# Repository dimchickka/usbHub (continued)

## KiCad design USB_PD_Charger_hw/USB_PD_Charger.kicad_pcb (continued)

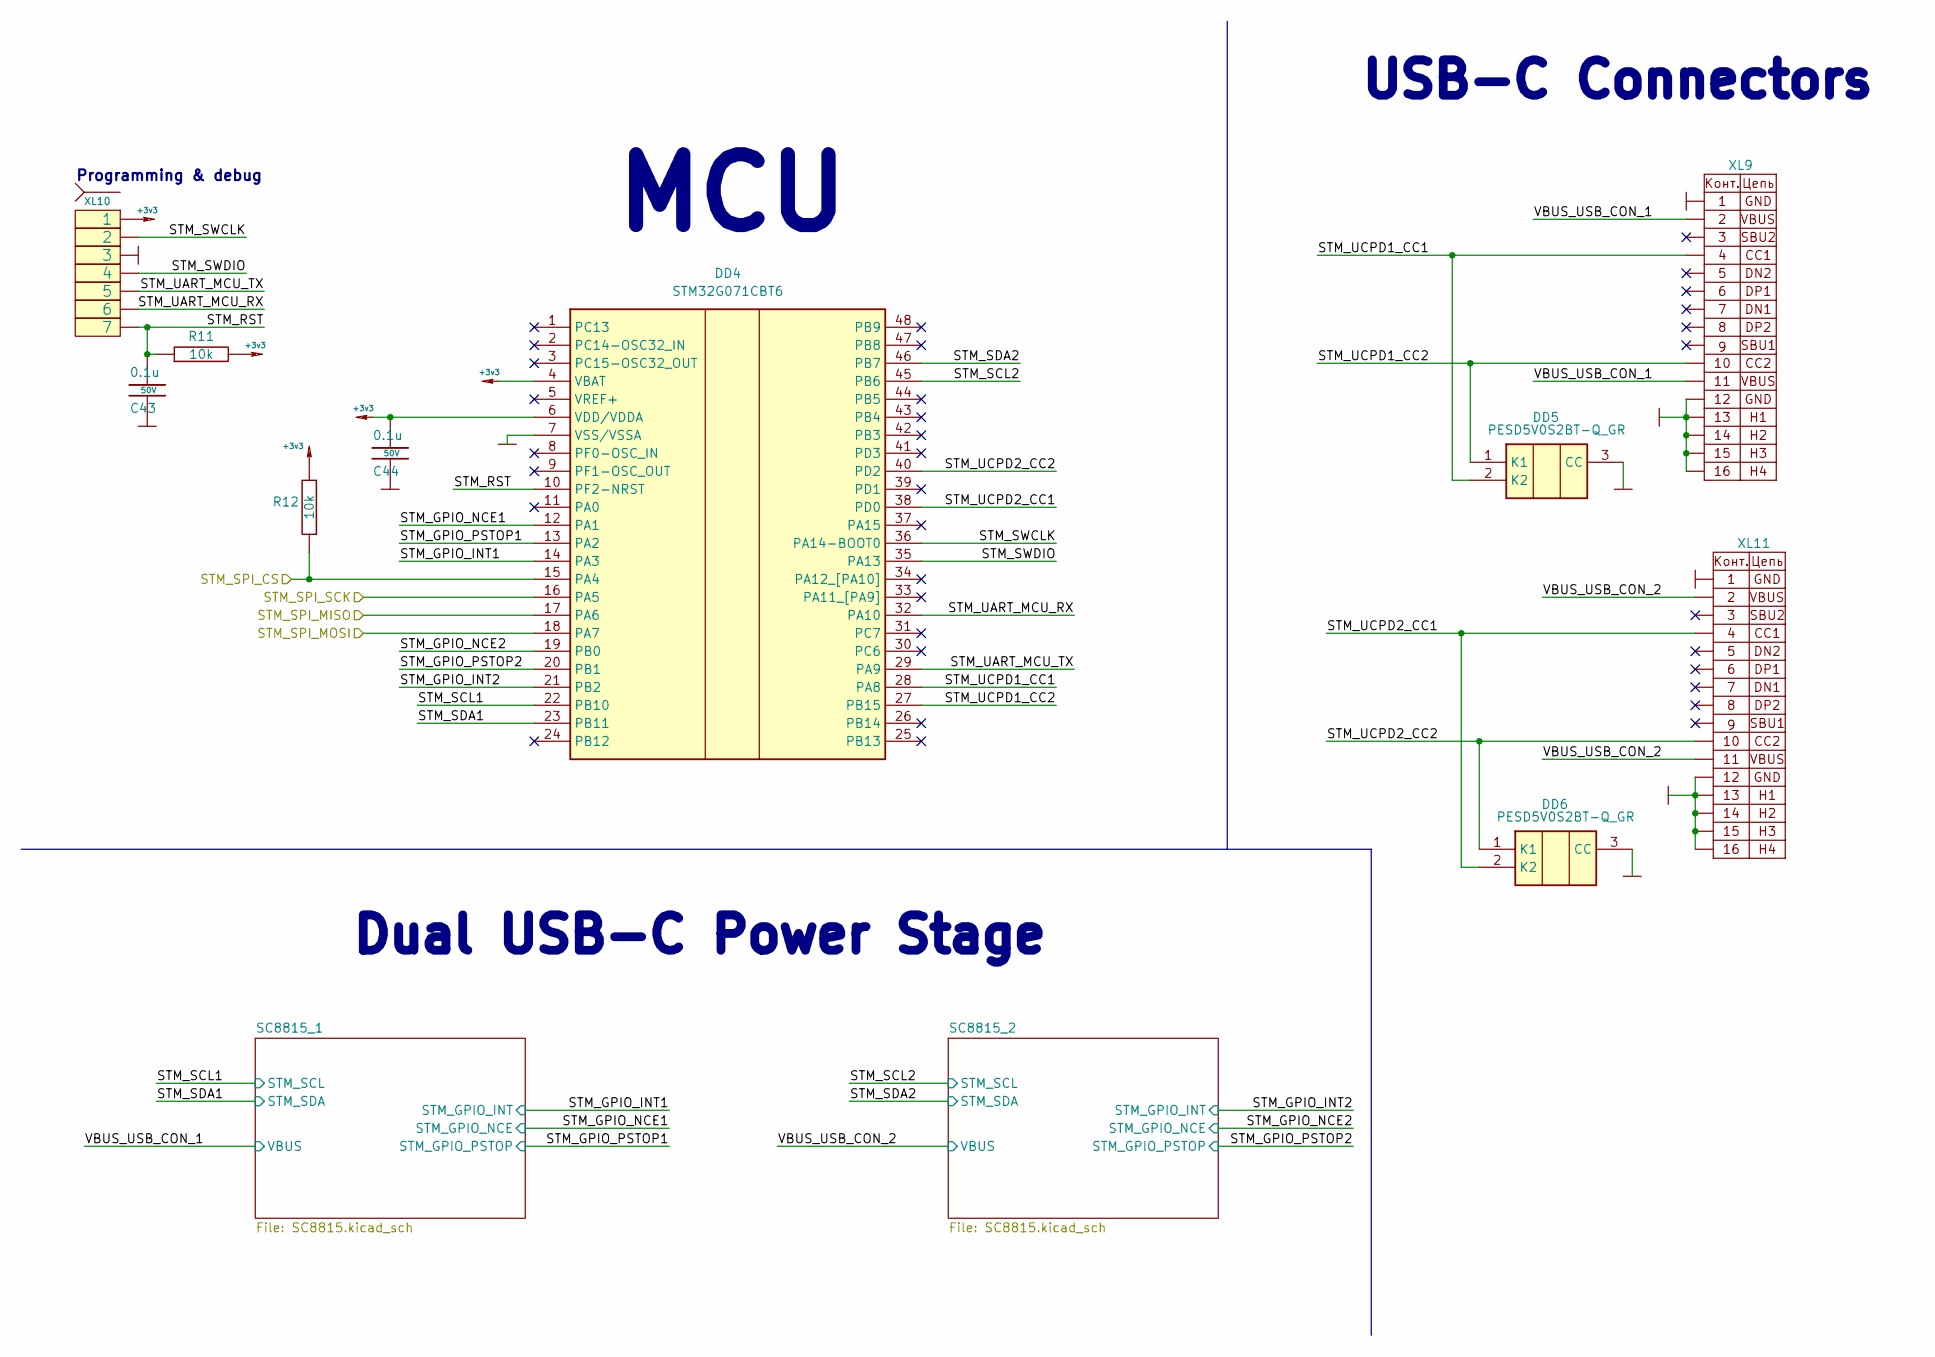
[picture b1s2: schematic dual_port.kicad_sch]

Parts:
C43, C44: 0.1u; CAP_0603_Silks; Tolerance 10%; Voltage 50V
DD4: STM32G071CBT6; QFP50P900X900X160-48N; Manufacturer_Part_Number STM32G071CBT6; Mouser Part Number 511-STM32G071CBT6
DD5, DD6: PESD5V0S2BT-Q_GR; SOT95P230X110-3N; Manufacturer_Part_Number PESD5V0S2BT-Q/GR
R11, R12: 10k; RES_0603_Silks; Tolerance 1%
XL9, XL11: USBC_DS1144-18
XL10: SOCKET_7; PLS-7_LOCK

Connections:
+3v3: C44.1, DD4.4 (VBAT), DD4.6 (VDD/VDDA), R11.2, R12.2, XL10.1; also elsewhere on the board
/Dual_USB_C_ports_1/STM_GPIO_INT1: DD4.14 (PA3); also elsewhere on the board
/Dual_USB_C_ports_1/STM_GPIO_INT2: DD4.21 (PB2); also elsewhere on the board
/Dual_USB_C_ports_1/STM_GPIO_NCE1: DD4.12 (PA1); also elsewhere on the board
/Dual_USB_C_ports_1/STM_GPIO_NCE2: DD4.19 (PB0); also elsewhere on the board
/Dual_USB_C_ports_1/STM_GPIO_PSTOP1: DD4.13 (PA2); also elsewhere on the board
/Dual_USB_C_ports_1/STM_GPIO_PSTOP2: DD4.20 (PB1); also elsewhere on the board
/Dual_USB_C_ports_1/STM_RST: C43.1, DD4.10 (PF2-NRST), R11.1, XL10.7
/Dual_USB_C_ports_1/STM_SCL1: DD4.22 (PB10); also elsewhere on the board
/Dual_USB_C_ports_1/STM_SCL2: DD4.45 (PB6); also elsewhere on the board
/Dual_USB_C_ports_1/STM_SDA1: DD4.23 (PB11); also elsewhere on the board
/Dual_USB_C_ports_1/STM_SDA2: DD4.46 (PB7); also elsewhere on the board
/Dual_USB_C_ports_1/STM_SWCLK: DD4.36 (PA14-BOOT0), XL10.2
/Dual_USB_C_ports_1/STM_SWDIO: DD4.35 (PA13), XL10.4
/Dual_USB_C_ports_1/STM_UART_MCU_RX: DD4.32 (PA10), XL10.6
/Dual_USB_C_ports_1/STM_UART_MCU_TX: DD4.29 (PA9), XL10.5
/Dual_USB_C_ports_1/STM_UCPD1_CC1: DD4.28 (PA8), DD5.2 (K2), XL9.A5 (r1t0)
/Dual_USB_C_ports_1/STM_UCPD1_CC2: DD4.27 (PB15), DD5.1 (K1), XL9.B5 (r3t0)
/Dual_USB_C_ports_1/STM_UCPD2_CC1: DD4.38 (PD0), DD6.2 (K2), XL11.A5 (r1t0)
/Dual_USB_C_ports_1/STM_UCPD2_CC2: DD4.40 (PD2), DD6.1 (K1), XL11.B5 (r3t0)
/Dual_USB_C_ports_1/VBUS_USB_CON_1: XL9.A4B9 (rot1), XL9.B4A9 (r3t1); also elsewhere on the board
/Dual_USB_C_ports_1/VBUS_USB_CON_2: XL11.A4B9 (rot1), XL11.B4A9 (r3t1); also elsewhere on the board
/STM1_CS: DD4.15 (PA4), R12.1; also elsewhere on the board
/STM_MISO: DD4.17 (PA6); also elsewhere on the board
/STM_MOSI: DD4.18 (PA7); also elsewhere on the board
/STM_SCK: DD4.16 (PA5); also elsewhere on the board
GND: C43.2, C44.2, DD4.7 (VSS/VSSA), DD5.3 (CC), DD6.3 (CC), XL9.A1B12 (rot0), XL9.B1A12 (+3.3V), XL9.H1 (r3t0), XL9.H2 (r3t0), XL9.H3, XL9.H4 (+3.3V), XL10.3, XL11.A1B12 (rot0), XL11.B1A12 (+3.3V), XL11.H1 (r3t0), XL11.H2 (r3t0), XL11.H3, XL11.H4 (+3.3V); also elsewhere on the board

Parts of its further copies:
C93, C94, C143, C144, C193, C194, C243, C244, C293, C294, C343, C344, C393, C394, C443, C444, C493, C494: 0.1u; CAP_0603_Silks; Tolerance 10%; Voltage 50V
DD9, DD14, DD19, DD24, DD29, DD34, DD39, DD44, DD49: STM32G071CBT6; QFP50P900X900X160-48N; Manufacturer_Part_Number STM32G071CBT6; Mouser Part Number 511-STM32G071CBT6
DD10, DD11, DD15, DD16, DD20, DD21, DD25, DD26, DD30, DD31, DD35, DD36, DD40, DD41, DD45, DD46, DD50, DD51: PESD5V0S2BT-Q_GR; SOT95P230X110-3N; Manufacturer_Part_Number PESD5V0S2BT-Q/GR
R55, R56, R99, R100, R143, R144, R187, R188, R231, R232, R275, R276, R319, R320, R363, R364, R407, R408: 10k; RES_0603_Silks; Tolerance 1%
XL12, XL14, XL15, XL17, XL18, XL20, XL21, XL23, XL24, XL26, XL27, XL29, XL30, XL32, XL33, XL35, XL36, XL38: USBC_DS1144-18
XL13, XL16, XL19, XL22, XL25, XL28, XL31, XL34, XL37: SOCKET_7; PLS-7_LOCK

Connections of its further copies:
+3v3: C94.1, C144.1, C194.1, C244.1, C294.1, C344.1, C394.1, C444.1, C494.1, DD9.4 (VBAT), DD9.6 (VDD/VDDA), DD14.4 (VBAT), DD14.6 (VDD/VDDA), DD19.4 (VBAT), DD19.6 (VDD/VDDA), DD24.4 (VBAT), DD24.6 (VDD/VDDA), DD29.4 (VBAT), DD29.6 (VDD/VDDA), DD34.4 (VBAT), DD34.6 (VDD/VDDA), DD39.4 (VBAT), DD39.6 (VDD/VDDA), DD44.4 (VBAT), DD44.6 (VDD/VDDA), DD49.4 (VBAT), DD49.6 (VDD/VDDA), R55.2, R56.2, R99.2, R100.2, R143.2, R144.2, R187.2, R188.2, R231.2, R232.2, R275.2, R276.2, R319.2, R320.2, R363.2, R364.2, R407.2, R408.2, XL13.1, XL16.1, XL19.1, XL22.1, XL25.1, XL28.1, XL31.1, XL34.1, XL37.1; also elsewhere on the board
/Dual_USB_C_ports_2/STM_GPIO_INT1: DD9.14 (PA3); also elsewhere on the board
/Dual_USB_C_ports_2/STM_GPIO_INT2: DD9.21 (PB2); also elsewhere on the board
/Dual_USB_C_ports_2/STM_GPIO_NCE1: DD9.12 (PA1); also elsewhere on the board
/Dual_USB_C_ports_2/STM_GPIO_NCE2: DD9.19 (PB0); also elsewhere on the board
/Dual_USB_C_ports_2/STM_GPIO_PSTOP1: DD9.13 (PA2); also elsewhere on the board
/Dual_USB_C_ports_2/STM_GPIO_PSTOP2: DD9.20 (PB1); also elsewhere on the board
/Dual_USB_C_ports_2/STM_RST: C93.1, DD9.10 (PF2-NRST), R55.1, XL13.7
/Dual_USB_C_ports_2/STM_SCL1: DD9.22 (PB10); also elsewhere on the board
/Dual_USB_C_ports_2/STM_SCL2: DD9.45 (PB6); also elsewhere on the board
/Dual_USB_C_ports_2/STM_SDA1: DD9.23 (PB11); also elsewhere on the board
/Dual_USB_C_ports_2/STM_SDA2: DD9.46 (PB7); also elsewhere on the board
/Dual_USB_C_ports_2/STM_SWCLK: DD9.36 (PA14-BOOT0), XL13.2
/Dual_USB_C_ports_2/STM_SWDIO: DD9.35 (PA13), XL13.4
/Dual_USB_C_ports_2/STM_UART_MCU_RX: DD9.32 (PA10), XL13.6
/Dual_USB_C_ports_2/STM_UART_MCU_TX: DD9.29 (PA9), XL13.5
/Dual_USB_C_ports_2/STM_UCPD1_CC1: DD9.28 (PA8), DD10.2 (K2), XL12.A5 (r1t0)
/Dual_USB_C_ports_2/STM_UCPD1_CC2: DD9.27 (PB15), DD10.1 (K1), XL12.B5 (r3t0)
/Dual_USB_C_ports_2/STM_UCPD2_CC1: DD9.38 (PD0), DD11.2 (K2), XL14.A5 (r1t0)
/Dual_USB_C_ports_2/STM_UCPD2_CC2: DD9.40 (PD2), DD11.1 (K1), XL14.B5 (r3t0)
/Dual_USB_C_ports_2/VBUS_USB_CON_1: XL12.A4B9 (rot1), XL12.B4A9 (r3t1); also elsewhere on the board
/Dual_USB_C_ports_2/VBUS_USB_CON_2: XL14.A4B9 (rot1), XL14.B4A9 (r3t1); also elsewhere on the board
/Dual_USB_C_ports_3/STM_GPIO_INT1: DD14.14 (PA3); also elsewhere on the board
/Dual_USB_C_ports_3/STM_GPIO_INT2: DD14.21 (PB2); also elsewhere on the board
/Dual_USB_C_ports_3/STM_GPIO_NCE1: DD14.12 (PA1); also elsewhere on the board
/Dual_USB_C_ports_3/STM_GPIO_NCE2: DD14.19 (PB0); also elsewhere on the board
/Dual_USB_C_ports_3/STM_GPIO_PSTOP1: DD14.13 (PA2); also elsewhere on the board
/Dual_USB_C_ports_3/STM_GPIO_PSTOP2: DD14.20 (PB1); also elsewhere on the board
/Dual_USB_C_ports_3/STM_RST: C143.1, DD14.10 (PF2-NRST), R99.1, XL16.7
/Dual_USB_C_ports_3/STM_SCL1: DD14.22 (PB10); also elsewhere on the board
/Dual_USB_C_ports_3/STM_SCL2: DD14.45 (PB6); also elsewhere on the board
/Dual_USB_C_ports_3/STM_SDA1: DD14.23 (PB11); also elsewhere on the board
/Dual_USB_C_ports_3/STM_SDA2: DD14.46 (PB7); also elsewhere on the board
/Dual_USB_C_ports_3/STM_SWCLK: DD14.36 (PA14-BOOT0), XL16.2
/Dual_USB_C_ports_3/STM_SWDIO: DD14.35 (PA13), XL16.4
/Dual_USB_C_ports_3/STM_UART_MCU_RX: DD14.32 (PA10), XL16.6
/Dual_USB_C_ports_3/STM_UART_MCU_TX: DD14.29 (PA9), XL16.5
/Dual_USB_C_ports_3/STM_UCPD1_CC1: DD14.28 (PA8), DD15.2 (K2), XL15.A5 (r1t0)
/Dual_USB_C_ports_3/STM_UCPD1_CC2: DD14.27 (PB15), DD15.1 (K1), XL15.B5 (r3t0)
/Dual_USB_C_ports_3/STM_UCPD2_CC1: DD14.38 (PD0), DD16.2 (K2), XL17.A5 (r1t0)
/Dual_USB_C_ports_3/STM_UCPD2_CC2: DD14.40 (PD2), DD16.1 (K1), XL17.B5 (r3t0)
/Dual_USB_C_ports_3/VBUS_USB_CON_1: XL15.A4B9 (rot1), XL15.B4A9 (r3t1); also elsewhere on the board
/Dual_USB_C_ports_3/VBUS_USB_CON_2: XL17.A4B9 (rot1), XL17.B4A9 (r3t1); also elsewhere on the board
/Dual_USB_C_ports_4/STM_GPIO_INT1: DD19.14 (PA3); also elsewhere on the board
/Dual_USB_C_ports_4/STM_GPIO_INT2: DD19.21 (PB2); also elsewhere on the board
/Dual_USB_C_ports_4/STM_GPIO_NCE1: DD19.12 (PA1); also elsewhere on the board
/Dual_USB_C_ports_4/STM_GPIO_NCE2: DD19.19 (PB0); also elsewhere on the board
/Dual_USB_C_ports_4/STM_GPIO_PSTOP1: DD19.13 (PA2); also elsewhere on the board
/Dual_USB_C_ports_4/STM_GPIO_PSTOP2: DD19.20 (PB1); also elsewhere on the board
/Dual_USB_C_ports_4/STM_RST: C193.1, DD19.10 (PF2-NRST), R143.1, XL19.7
/Dual_USB_C_ports_4/STM_SCL1: DD19.22 (PB10); also elsewhere on the board
/Dual_USB_C_ports_4/STM_SCL2: DD19.45 (PB6); also elsewhere on the board
/Dual_USB_C_ports_4/STM_SDA1: DD19.23 (PB11); also elsewhere on the board
/Dual_USB_C_ports_4/STM_SDA2: DD19.46 (PB7); also elsewhere on the board
/Dual_USB_C_ports_4/STM_SWCLK: DD19.36 (PA14-BOOT0), XL19.2
/Dual_USB_C_ports_4/STM_SWDIO: DD19.35 (PA13), XL19.4
/Dual_USB_C_ports_4/STM_UART_MCU_RX: DD19.32 (PA10), XL19.6
/Dual_USB_C_ports_4/STM_UART_MCU_TX: DD19.29 (PA9), XL19.5
/Dual_USB_C_ports_4/STM_UCPD1_CC1: DD19.28 (PA8), DD20.2 (K2), XL18.A5 (r1t0)
/Dual_USB_C_ports_4/STM_UCPD1_CC2: DD19.27 (PB15), DD20.1 (K1), XL18.B5 (r3t0)
/Dual_USB_C_ports_4/STM_UCPD2_CC1: DD19.38 (PD0), DD21.2 (K2), XL20.A5 (r1t0)
/Dual_USB_C_ports_4/STM_UCPD2_CC2: DD19.40 (PD2), DD21.1 (K1), XL20.B5 (r3t0)
/Dual_USB_C_ports_4/VBUS_USB_CON_1: XL18.A4B9 (rot1), XL18.B4A9 (r3t1); also elsewhere on the board
/Dual_USB_C_ports_4/VBUS_USB_CON_2: XL20.A4B9 (rot1), XL20.B4A9 (r3t1); also elsewhere on the board
/Dual_USB_C_ports_5/STM_GPIO_INT1: DD24.14 (PA3); also elsewhere on the board
/Dual_USB_C_ports_5/STM_GPIO_INT2: DD24.21 (PB2); also elsewhere on the board
/Dual_USB_C_ports_5/STM_GPIO_NCE1: DD24.12 (PA1); also elsewhere on the board
/Dual_USB_C_ports_5/STM_GPIO_NCE2: DD24.19 (PB0); also elsewhere on the board
/Dual_USB_C_ports_5/STM_GPIO_PSTOP1: DD24.13 (PA2); also elsewhere on the board
/Dual_USB_C_ports_5/STM_GPIO_PSTOP2: DD24.20 (PB1); also elsewhere on the board
/Dual_USB_C_ports_5/STM_RST: C243.1, DD24.10 (PF2-NRST), R187.1, XL22.7
/Dual_USB_C_ports_5/STM_SCL1: DD24.22 (PB10); also elsewhere on the board
/Dual_USB_C_ports_5/STM_SCL2: DD24.45 (PB6); also elsewhere on the board
/Dual_USB_C_ports_5/STM_SDA1: DD24.23 (PB11); also elsewhere on the board
/Dual_USB_C_ports_5/STM_SDA2: DD24.46 (PB7); also elsewhere on the board
/Dual_USB_C_ports_5/STM_SWCLK: DD24.36 (PA14-BOOT0), XL22.2
/Dual_USB_C_ports_5/STM_SWDIO: DD24.35 (PA13), XL22.4
/Dual_USB_C_ports_5/STM_UART_MCU_RX: DD24.32 (PA10), XL22.6
/Dual_USB_C_ports_5/STM_UART_MCU_TX: DD24.29 (PA9), XL22.5
/Dual_USB_C_ports_5/STM_UCPD1_CC1: DD24.28 (PA8), DD25.2 (K2), XL21.A5 (r1t0)
/Dual_USB_C_ports_5/STM_UCPD1_CC2: DD24.27 (PB15), DD25.1 (K1), XL21.B5 (r3t0)
/Dual_USB_C_ports_5/STM_UCPD2_CC1: DD24.38 (PD0), DD26.2 (K2), XL23.A5 (r1t0)
/Dual_USB_C_ports_5/STM_UCPD2_CC2: DD24.40 (PD2), DD26.1 (K1), XL23.B5 (r3t0)
/Dual_USB_C_ports_5/VBUS_USB_CON_1: XL21.A4B9 (rot1), XL21.B4A9 (r3t1); also elsewhere on the board
/Dual_USB_C_ports_5/VBUS_USB_CON_2: XL23.A4B9 (rot1), XL23.B4A9 (r3t1); also elsewhere on the board
/Dual_USB_C_ports_6/STM_GPIO_INT1: DD29.14 (PA3); also elsewhere on the board
/Dual_USB_C_ports_6/STM_GPIO_INT2: DD29.21 (PB2); also elsewhere on the board
/Dual_USB_C_ports_6/STM_GPIO_NCE1: DD29.12 (PA1); also elsewhere on the board
/Dual_USB_C_ports_6/STM_GPIO_NCE2: DD29.19 (PB0); also elsewhere on the board
/Dual_USB_C_ports_6/STM_GPIO_PSTOP1: DD29.13 (PA2); also elsewhere on the board
/Dual_USB_C_ports_6/STM_GPIO_PSTOP2: DD29.20 (PB1); also elsewhere on the board
/Dual_USB_C_ports_6/STM_RST: C293.1, DD29.10 (PF2-NRST), R231.1, XL25.7
/Dual_USB_C_ports_6/STM_SCL1: DD29.22 (PB10); also elsewhere on the board
/Dual_USB_C_ports_6/STM_SCL2: DD29.45 (PB6); also elsewhere on the board
/Dual_USB_C_ports_6/STM_SDA1: DD29.23 (PB11); also elsewhere on the board
/Dual_USB_C_ports_6/STM_SDA2: DD29.46 (PB7); also elsewhere on the board
/Dual_USB_C_ports_6/STM_SWCLK: DD29.36 (PA14-BOOT0), XL25.2
/Dual_USB_C_ports_6/STM_SWDIO: DD29.35 (PA13), XL25.4
/Dual_USB_C_ports_6/STM_UART_MCU_RX: DD29.32 (PA10), XL25.6
/Dual_USB_C_ports_6/STM_UART_MCU_TX: DD29.29 (PA9), XL25.5
/Dual_USB_C_ports_6/STM_UCPD1_CC1: DD29.28 (PA8), DD30.2 (K2), XL24.A5 (r1t0)
/Dual_USB_C_ports_6/STM_UCPD1_CC2: DD29.27 (PB15), DD30.1 (K1), XL24.B5 (r3t0)
/Dual_USB_C_ports_6/STM_UCPD2_CC1: DD29.38 (PD0), DD31.2 (K2), XL26.A5 (r1t0)
/Dual_USB_C_ports_6/STM_UCPD2_CC2: DD29.40 (PD2), DD31.1 (K1), XL26.B5 (r3t0)
/Dual_USB_C_ports_6/VBUS_USB_CON_1: XL24.A4B9 (rot1), XL24.B4A9 (r3t1); also elsewhere on the board
/Dual_USB_C_ports_6/VBUS_USB_CON_2: XL26.A4B9 (rot1), XL26.B4A9 (r3t1); also elsewhere on the board
/Dual_USB_C_ports_7/STM_GPIO_INT1: DD34.14 (PA3); also elsewhere on the board
/Dual_USB_C_ports_7/STM_GPIO_INT2: DD34.21 (PB2); also elsewhere on the board
/Dual_USB_C_ports_7/STM_GPIO_NCE1: DD34.12 (PA1); also elsewhere on the board
/Dual_USB_C_ports_7/STM_GPIO_NCE2: DD34.19 (PB0); also elsewhere on the board
/Dual_USB_C_ports_7/STM_GPIO_PSTOP1: DD34.13 (PA2); also elsewhere on the board
/Dual_USB_C_ports_7/STM_GPIO_PSTOP2: DD34.20 (PB1); also elsewhere on the board
/Dual_USB_C_ports_7/STM_RST: C343.1, DD34.10 (PF2-NRST), R275.1, XL28.7
/Dual_USB_C_ports_7/STM_SCL1: DD34.22 (PB10); also elsewhere on the board
/Dual_USB_C_ports_7/STM_SCL2: DD34.45 (PB6); also elsewhere on the board
/Dual_USB_C_ports_7/STM_SDA1: DD34.23 (PB11); also elsewhere on the board
/Dual_USB_C_ports_7/STM_SDA2: DD34.46 (PB7); also elsewhere on the board
/Dual_USB_C_ports_7/STM_SWCLK: DD34.36 (PA14-BOOT0), XL28.2
/Dual_USB_C_ports_7/STM_SWDIO: DD34.35 (PA13), XL28.4
/Dual_USB_C_ports_7/STM_UART_MCU_RX: DD34.32 (PA10), XL28.6
/Dual_USB_C_ports_7/STM_UART_MCU_TX: DD34.29 (PA9), XL28.5
/Dual_USB_C_ports_7/STM_UCPD1_CC1: DD34.28 (PA8), DD35.2 (K2), XL27.A5 (r1t0)
/Dual_USB_C_ports_7/STM_UCPD1_CC2: DD34.27 (PB15), DD35.1 (K1), XL27.B5 (r3t0)
/Dual_USB_C_ports_7/STM_UCPD2_CC1: DD34.38 (PD0), DD36.2 (K2), XL29.A5 (r1t0)
/Dual_USB_C_ports_7/STM_UCPD2_CC2: DD34.40 (PD2), DD36.1 (K1), XL29.B5 (r3t0)
/Dual_USB_C_ports_7/VBUS_USB_CON_1: XL27.A4B9 (rot1), XL27.B4A9 (r3t1); also elsewhere on the board
/Dual_USB_C_ports_7/VBUS_USB_CON_2: XL29.A4B9 (rot1), XL29.B4A9 (r3t1); also elsewhere on the board
/Dual_USB_C_ports_8/STM_GPIO_INT1: DD39.14 (PA3); also elsewhere on the board
/Dual_USB_C_ports_8/STM_GPIO_INT2: DD39.21 (PB2); also elsewhere on the board
/Dual_USB_C_ports_8/STM_GPIO_NCE1: DD39.12 (PA1); also elsewhere on the board
/Dual_USB_C_ports_8/STM_GPIO_NCE2: DD39.19 (PB0); also elsewhere on the board
/Dual_USB_C_ports_8/STM_GPIO_PSTOP1: DD39.13 (PA2); also elsewhere on the board
/Dual_USB_C_ports_8/STM_GPIO_PSTOP2: DD39.20 (PB1); also elsewhere on the board
/Dual_USB_C_ports_8/STM_RST: C393.1, DD39.10 (PF2-NRST), R319.1, XL31.7
/Dual_USB_C_ports_8/STM_SCL1: DD39.22 (PB10); also elsewhere on the board
/Dual_USB_C_ports_8/STM_SCL2: DD39.45 (PB6); also elsewhere on the board
/Dual_USB_C_ports_8/STM_SDA1: DD39.23 (PB11); also elsewhere on the board
/Dual_USB_C_ports_8/STM_SDA2: DD39.46 (PB7); also elsewhere on the board
/Dual_USB_C_ports_8/STM_SWCLK: DD39.36 (PA14-BOOT0), XL31.2
/Dual_USB_C_ports_8/STM_SWDIO: DD39.35 (PA13), XL31.4
/Dual_USB_C_ports_8/STM_UART_MCU_RX: DD39.32 (PA10), XL31.6
/Dual_USB_C_ports_8/STM_UART_MCU_TX: DD39.29 (PA9), XL31.5
/Dual_USB_C_ports_8/STM_UCPD1_CC1: DD39.28 (PA8), DD40.2 (K2), XL30.A5 (r1t0)
/Dual_USB_C_ports_8/STM_UCPD1_CC2: DD39.27 (PB15), DD40.1 (K1), XL30.B5 (r3t0)
/Dual_USB_C_ports_8/STM_UCPD2_CC1: DD39.38 (PD0), DD41.2 (K2), XL32.A5 (r1t0)
/Dual_USB_C_ports_8/STM_UCPD2_CC2: DD39.40 (PD2), DD41.1 (K1), XL32.B5 (r3t0)
/Dual_USB_C_ports_8/VBUS_USB_CON_1: XL30.A4B9 (rot1), XL30.B4A9 (r3t1); also elsewhere on the board
/Dual_USB_C_ports_8/VBUS_USB_CON_2: XL32.A4B9 (rot1), XL32.B4A9 (r3t1); also elsewhere on the board
/Dual_USB_C_ports_9/STM_GPIO_INT1: DD44.14 (PA3); also elsewhere on the board
/Dual_USB_C_ports_9/STM_GPIO_INT2: DD44.21 (PB2); also elsewhere on the board
/Dual_USB_C_ports_9/STM_GPIO_NCE1: DD44.12 (PA1); also elsewhere on the board
/Dual_USB_C_ports_9/STM_GPIO_NCE2: DD44.19 (PB0); also elsewhere on the board
/Dual_USB_C_ports_9/STM_GPIO_PSTOP1: DD44.13 (PA2); also elsewhere on the board
/Dual_USB_C_ports_9/STM_GPIO_PSTOP2: DD44.20 (PB1); also elsewhere on the board
/Dual_USB_C_ports_9/STM_RST: C443.1, DD44.10 (PF2-NRST), R363.1, XL34.7
/Dual_USB_C_ports_9/STM_SCL1: DD44.22 (PB10); also elsewhere on the board
/Dual_USB_C_ports_9/STM_SCL2: DD44.45 (PB6); also elsewhere on the board
/Dual_USB_C_ports_9/STM_SDA1: DD44.23 (PB11); also elsewhere on the board
/Dual_USB_C_ports_9/STM_SDA2: DD44.46 (PB7); also elsewhere on the board
/Dual_USB_C_ports_9/STM_SWCLK: DD44.36 (PA14-BOOT0), XL34.2
/Dual_USB_C_ports_9/STM_SWDIO: DD44.35 (PA13), XL34.4
/Dual_USB_C_ports_9/STM_UART_MCU_RX: DD44.32 (PA10), XL34.6
/Dual_USB_C_ports_9/STM_UART_MCU_TX: DD44.29 (PA9), XL34.5
/Dual_USB_C_ports_9/STM_UCPD1_CC1: DD44.28 (PA8), DD45.2 (K2), XL33.A5 (r1t0)
/Dual_USB_C_ports_9/STM_UCPD1_CC2: DD44.27 (PB15), DD45.1 (K1), XL33.B5 (r3t0)
/Dual_USB_C_ports_9/STM_UCPD2_CC1: DD44.38 (PD0), DD46.2 (K2), XL35.A5 (r1t0)
/Dual_USB_C_ports_9/STM_UCPD2_CC2: DD44.40 (PD2), DD46.1 (K1), XL35.B5 (r3t0)
/Dual_USB_C_ports_9/VBUS_USB_CON_1: XL33.A4B9 (rot1), XL33.B4A9 (r3t1); also elsewhere on the board
/Dual_USB_C_ports_9/VBUS_USB_CON_2: XL35.A4B9 (rot1), XL35.B4A9 (r3t1); also elsewhere on the board
/Dual_USB_C_ports_10/STM_GPIO_INT1: DD49.14 (PA3); also elsewhere on the board
/Dual_USB_C_ports_10/STM_GPIO_INT2: DD49.21 (PB2); also elsewhere on the board
/Dual_USB_C_ports_10/STM_GPIO_NCE1: DD49.12 (PA1); also elsewhere on the board
/Dual_USB_C_ports_10/STM_GPIO_NCE2: DD49.19 (PB0); also elsewhere on the board
/Dual_USB_C_ports_10/STM_GPIO_PSTOP1: DD49.13 (PA2); also elsewhere on the board
/Dual_USB_C_ports_10/STM_GPIO_PSTOP2: DD49.20 (PB1); also elsewhere on the board
/Dual_USB_C_ports_10/STM_RST: C493.1, DD49.10 (PF2-NRST), R407.1, XL37.7
/Dual_USB_C_ports_10/STM_SCL1: DD49.22 (PB10); also elsewhere on the board
/Dual_USB_C_ports_10/STM_SCL2: DD49.45 (PB6); also elsewhere on the board
/Dual_USB_C_ports_10/STM_SDA1: DD49.23 (PB11); also elsewhere on the board
/Dual_USB_C_ports_10/STM_SDA2: DD49.46 (PB7); also elsewhere on the board
/Dual_USB_C_ports_10/STM_SWCLK: DD49.36 (PA14-BOOT0), XL37.2
/Dual_USB_C_ports_10/STM_SWDIO: DD49.35 (PA13), XL37.4
/Dual_USB_C_ports_10/STM_UART_MCU_RX: DD49.32 (PA10), XL37.6
/Dual_USB_C_ports_10/STM_UART_MCU_TX: DD49.29 (PA9), XL37.5
/Dual_USB_C_ports_10/STM_UCPD1_CC1: DD49.28 (PA8), DD50.2 (K2), XL36.A5 (r1t0)
/Dual_USB_C_ports_10/STM_UCPD1_CC2: DD49.27 (PB15), DD50.1 (K1), XL36.B5 (r3t0)
/Dual_USB_C_ports_10/STM_UCPD2_CC1: DD49.38 (PD0), DD51.2 (K2), XL38.A5 (r1t0)
/Dual_USB_C_ports_10/STM_UCPD2_CC2: DD49.40 (PD2), DD51.1 (K1), XL38.B5 (r3t0)
/Dual_USB_C_ports_10/VBUS_USB_CON_1: XL36.A4B9 (rot1), XL36.B4A9 (r3t1); also elsewhere on the board
/Dual_USB_C_ports_10/VBUS_USB_CON_2: XL38.A4B9 (rot1), XL38.B4A9 (r3t1); also elsewhere on the board
/STM2_CS: DD14.15 (PA4), R100.1; also elsewhere on the board
/STM3_CS: DD24.15 (PA4), R188.1; also elsewhere on the board
/STM4_CS: DD34.15 (PA4), R276.1; also elsewhere on the board
/STM5_CS: DD44.15 (PA4), R364.1; also elsewhere on the board
/STM6_CS: DD9.15 (PA4), R56.1; also elsewhere on the board
/STM7_CS: DD19.15 (PA4), R144.1; also elsewhere on the board
/STM8_CS: DD29.15 (PA4), R232.1; also elsewhere on the board
/STM9_CS: DD39.15 (PA4), R320.1; also elsewhere on the board
/STM10_CS: DD49.15 (PA4), R408.1; also elsewhere on the board
/STM_MISO: DD9.17 (PA6), DD14.17 (PA6), DD19.17 (PA6), DD24.17 (PA6), DD29.17 (PA6), DD34.17 (PA6), DD39.17 (PA6), DD44.17 (PA6), DD49.17 (PA6); also elsewhere on the board
/STM_MOSI: DD9.18 (PA7), DD14.18 (PA7), DD19.18 (PA7), DD24.18 (PA7), DD29.18 (PA7), DD34.18 (PA7), DD39.18 (PA7), DD44.18 (PA7), DD49.18 (PA7); also elsewhere on the board
/STM_SCK: DD9.16 (PA5), DD14.16 (PA5), DD19.16 (PA5), DD24.16 (PA5), DD29.16 (PA5), DD34.16 (PA5), DD39.16 (PA5), DD44.16 (PA5), DD49.16 (PA5); also elsewhere on the board
GND: C93.2, C94.2, C143.2, C144.2, C193.2, C194.2, C243.2, C244.2, C293.2, C294.2, C343.2, C344.2, C393.2, C394.2, C443.2, C444.2, C493.2, C494.2, DD9.7 (VSS/VSSA), DD10.3 (CC), DD11.3 (CC), DD14.7 (VSS/VSSA), DD15.3 (CC), DD16.3 (CC), DD19.7 (VSS/VSSA), DD20.3 (CC), DD21.3 (CC), DD24.7 (VSS/VSSA), DD25.3 (CC), DD26.3 (CC), DD29.7 (VSS/VSSA), DD30.3 (CC), DD31.3 (CC), DD34.7 (VSS/VSSA), DD35.3 (CC), DD36.3 (CC), DD39.7 (VSS/VSSA), DD40.3 (CC), DD41.3 (CC), DD44.7 (VSS/VSSA), DD45.3 (CC), DD46.3 (CC), DD49.7 (VSS/VSSA), DD50.3 (CC), DD51.3 (CC), XL12.A1B12 (rot0), XL12.B1A12 (+3.3V), XL12.H1 (r3t0), XL12.H2 (r3t0), XL12.H3, XL12.H4 (+3.3V), XL13.3, XL14.A1B12 (rot0), XL14.B1A12 (+3.3V), XL14.H1 (r3t0), XL14.H2 (r3t0), XL14.H3, XL14.H4 (+3.3V), XL15.A1B12 (rot0), XL15.B1A12 (+3.3V), XL15.H1 (r3t0), XL15.H2 (r3t0), XL15.H3, XL15.H4 (+3.3V), XL16.3, XL17.A1B12 (rot0), XL17.B1A12 (+3.3V), XL17.H1 (r3t0), XL17.H2 (r3t0), XL17.H3, XL17.H4 (+3.3V), XL18.A1B12 (rot0), XL18.B1A12 (+3.3V), XL18.H1 (r3t0), XL18.H2 (r3t0), XL18.H3, XL18.H4 (+3.3V), XL19.3, XL20.A1B12 (rot0), XL20.B1A12 (+3.3V), XL20.H1 (r3t0), XL20.H2 (r3t0), XL20.H3, XL20.H4 (+3.3V), XL21.A1B12 (rot0), XL21.B1A12 (+3.3V), XL21.H1 (r3t0), XL21.H2 (r3t0), XL21.H3, XL21.H4 (+3.3V), XL22.3, XL23.A1B12 (rot0), XL23.B1A12 (+3.3V), XL23.H1 (r3t0), XL23.H2 (r3t0), XL23.H3, XL23.H4 (+3.3V), XL24.A1B12 (rot0), XL24.B1A12 (+3.3V), XL24.H1 (r3t0), XL24.H2 (r3t0), XL24.H3, XL24.H4 (+3.3V), XL25.3, XL26.A1B12 (rot0), XL26.B1A12 (+3.3V), XL26.H1 (r3t0), XL26.H2 (r3t0), XL26.H3, XL26.H4 (+3.3V), XL27.A1B12 (rot0), XL27.B1A12 (+3.3V), XL27.H1 (r3t0), XL27.H2 (r3t0), XL27.H3, XL27.H4 (+3.3V), XL28.3, XL29.A1B12 (rot0), XL29.B1A12 (+3.3V), XL29.H1 (r3t0), XL29.H2 (r3t0), XL29.H3, XL29.H4 (+3.3V), XL30.A1B12 (rot0), XL30.B1A12 (+3.3V), XL30.H1 (r3t0), XL30.H2 (r3t0), XL30.H3, XL30.H4 (+3.3V), XL31.3, XL32.A1B12 (rot0), XL32.B1A12 (+3.3V), XL32.H1 (r3t0), XL32.H2 (r3t0), XL32.H3, XL32.H4 (+3.3V), XL33.A1B12 (rot0), XL33.B1A12 (+3.3V), XL33.H1 (r3t0), XL33.H2 (r3t0), XL33.H3, XL33.H4 (+3.3V), XL34.3, XL35.A1B12 (rot0), XL35.B1A12 (+3.3V), XL35.H1 (r3t0), XL35.H2 (r3t0), XL35.H3, XL35.H4 (+3.3V), XL36.A1B12 (rot0), XL36.B1A12 (+3.3V), XL36.H1 (r3t0), XL36.H2 (r3t0), XL36.H3, XL36.H4 (+3.3V), XL37.3, XL38.A1B12 (rot0), XL38.B1A12 (+3.3V), XL38.H1 (r3t0), XL38.H2 (r3t0), XL38.H3, XL38.H4 (+3.3V); also elsewhere on the board

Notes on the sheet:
Programming & debug
USB-C Connectors
MCU
Dual USB-C Power Stage
